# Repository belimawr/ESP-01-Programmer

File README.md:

# ESP-01 Programmer

This programmer needs a external 3.3V, 0.5A power supply. The VCC pin
of the FTDI board is not connected because it can happen that the
current it can supply is not enough in some cases, leading to a
unstable behaviour.

## Schematic:

The RESET function/pin is not working in any of my breakout
boards. According to the
[Datasheet](https://www.espressif.com/sites/default/files/documentation/0a-esp8266ex_datasheet_en.pdf)
the RESET pin is active low, but it is not working on my breakout
boards. The workaround I found is to power-cycle the board every time
a reset is needed (including programming).

## Board library for Arduino IDE (1.8.13) programming

[esp8266/Arduino](https://github.com/esp8266/Arduino)
## Programming
Set the board parameters according to this picture:

Short the jumnper (JP1), hit "upload" then power-cycle the board. The
upload should run smoothly. If it does not, activate verbose output
for upload, then when you see this line:

`Connecting........_____`

Power-cycle the board again.

## Using I2C

The I2C bus uses `GPIO0` and `GPIO2`, those pins are available
on J3 and J4. To enable I2C on those pins, use `Wire.begin(0, 2);`.

[i2c_scanner.ino](i2c_scanner.ino) is an i2c scanner that shows how to
use the I2C bus on this board.

## Files

* [Schematic (PDF)](ESP01-Programmer.pdf)
* [3D board view](ESP01-Programmer_3D.png) - That is just a reference
  to help assembling on a prefboard
* [Kicad files](Kicad)

## Other resources
* [ESP-01 cheat
  sheet](esp8266_esp_01_module_pinout_diagram_cheat_sheet_by_adlerweb.png)
* [ESP-01 Manual](http://www.microchip.ua/wireless/esp01.pdf) - There
  is a schematic at the end
* [ESP-01 example applications](https://www.forward.com.au/pfod/ESP8266/GPIOpins/ESP8266_01_pin_magic.html)

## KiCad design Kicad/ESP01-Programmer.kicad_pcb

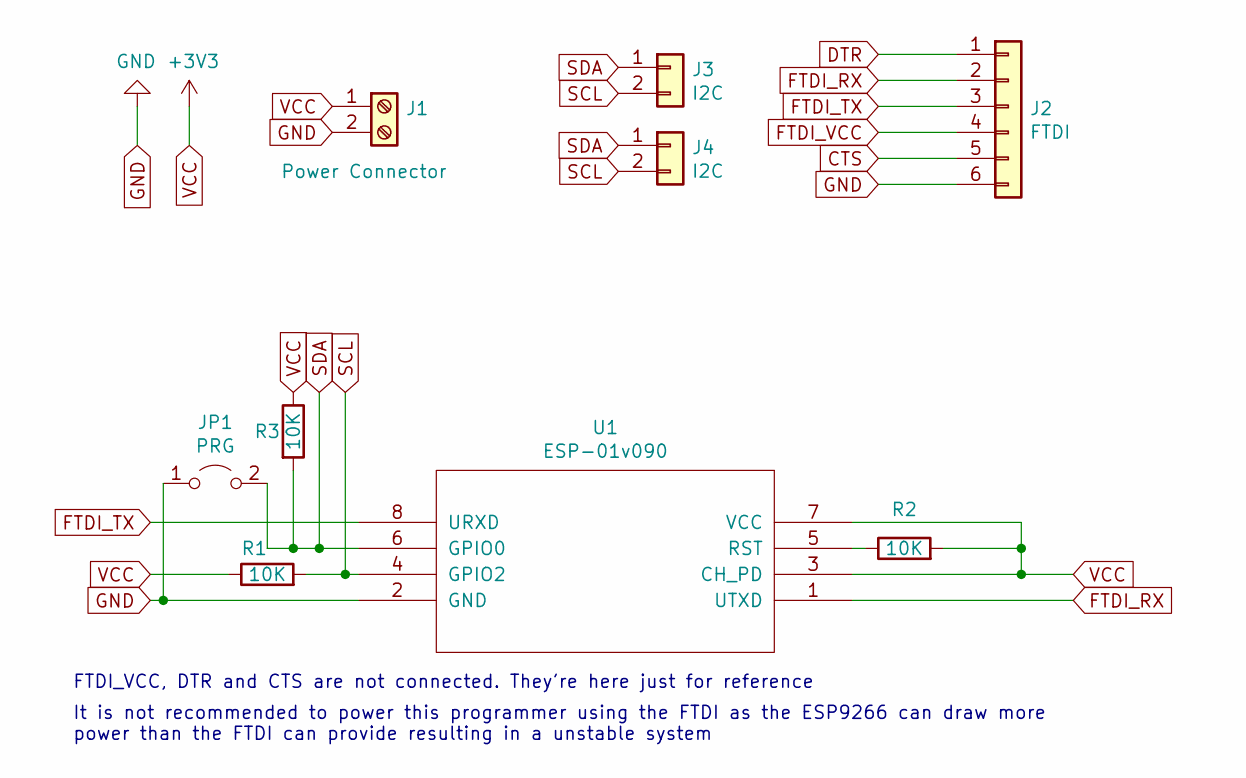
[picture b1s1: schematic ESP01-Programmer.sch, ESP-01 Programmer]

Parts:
J1: Power Connector; TerminalBlock_Phoenix_MKDS-1,5-2-5.08_1x02_P5.08mm_Horizont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
J2: FTDI; PinHeader_1x06_P2.54mm_Vertical
J3, J4: I2C; PinHeader_1x02_P2.54mm_Vertical
JP1: PRG; PinHeader_1x02_P2.54mm_Vertical
R1, R2, R3: 10K; R_Axial_DIN0207_L6.3mm_D2.5mm_P10.16mm_Horizontal
U1: ESP-01v090; ESP-01

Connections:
CTS: J2.5
DTR: J2.1
FTDI_RX: J2.2, U1.1 (UTXD)
FTDI_TX: J2.3, U1.8 (URXD)
FTDI_VCC: J2.4
GND: J1.2, J2.6, JP1.1 (A), U1.2 (GND)
unnamed: R2.1, U1.5 (RST)
SCL: J3.2, J4.2, R1.2, U1.4 (GPIO2)
SDA: J3.1, J4.1, JP1.2 (B), R3.2, U1.6 (GPIO0)
VCC: J1.1, R1.1, R2.2, R3.1, U1.3 (CH_PD), U1.7 (VCC)

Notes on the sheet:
FTDI_VCC, DTR and CTS are not connected. They're here just for reference
It is not recommended to power this programmer using the FTDI as the ESP9266 can draw more power than the FTDI can provide resulting in a unstable system

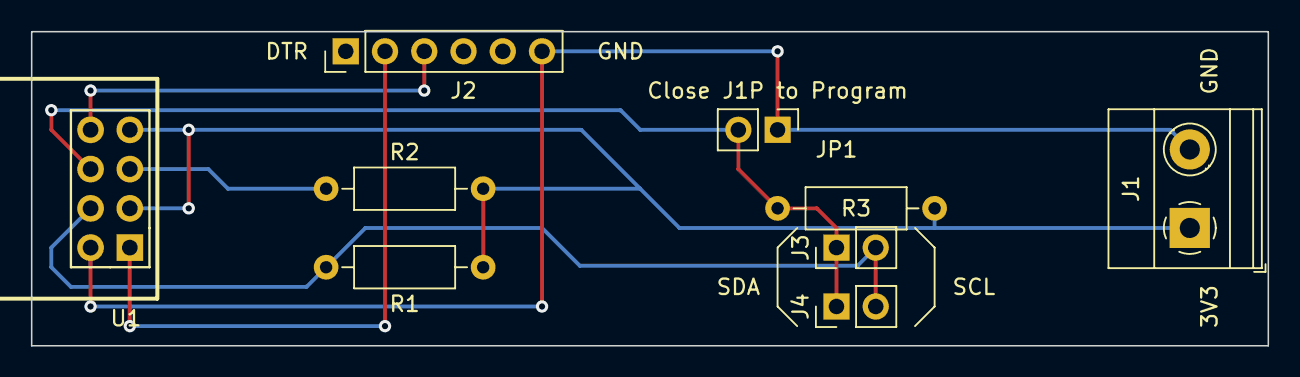
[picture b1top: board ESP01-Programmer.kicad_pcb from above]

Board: 2 copper layers, 80.0 x 20.3 mm, 9 parts (0 on the bottom side), 7 nets.

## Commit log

2020-07-28 V1.0: First working version
2020-07-28 V1.1: Adding I2C bus headers.
    More information and resources are also added.
